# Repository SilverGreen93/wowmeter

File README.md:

# Wow and Flutter meter

Implements the schematic found in Audio Magazine, year 1986, issue 6 to build a simple Wow and Flutter meter.

Contains PCB design.

This is a fork of https://dev.sigpipe.me/DashieElectronics/wowmeter

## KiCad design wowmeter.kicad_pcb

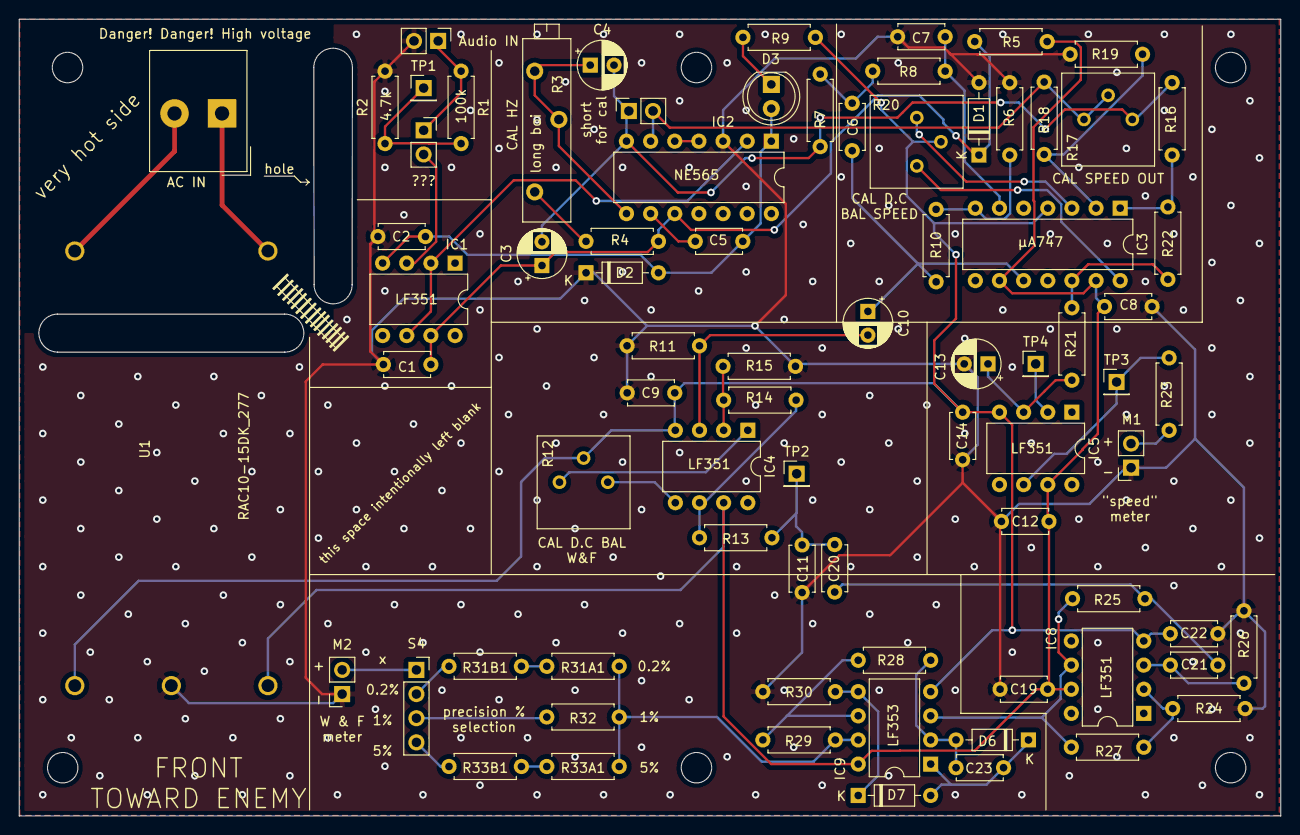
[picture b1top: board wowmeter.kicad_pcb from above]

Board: 2 copper layers, 132.7 x 83.8 mm, 84 parts (0 on the bottom side), 52 nets.

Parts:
C1, C2, C8, C9, C11, C12, C14, C19, C22: 0.022uF cerdisc; C_Disc_D4.7mm_W2.5mm_P5.00mm
C3: 0.1uF; CP_Radial_D5.0mm_P2.50mm
C4: 0.001uF; CP_Radial_D5.0mm_P2.50mm
C5, C6, C7: 0.01uF +-10% sty/mica; C_Disc_D4.7mm_W2.5mm_P5.00mm
C10, C13: 0.22uF; CP_Radial_D5.0mm_P2.50mm
C20, C21: 0.22uF +=10%; C_Disc_D4.7mm_W2.5mm_P5.00mm
C23: 100pF cerdisc; C_Disc_D4.7mm_W2.5mm_P5.00mm
D1, D2: 6V 500mW zener; D_DO-35_SOD27_P7.62mm_Horizontal
D3: LED; LED_D5.0mm
D6, D7: 1N4148; D_DO-35_SOD27_P7.62mm_Horizontal
H1, H2, H3, H4, H5, H6: MountingHole; MountingHole_3.2mm_M3
IC1, IC4, IC5, IC8: LF351; DIP-8_W7.62mm
IC2: NE565; DIP-14_W7.62mm
IC3: µA747; DIP-14_W7.62mm
IC9: LF353; DIP-8_W7.62mm
J1: Audio IN; PinHeader_1x02_P2.54mm_Vertical
J2: CAL_JMP; PinSocket_1x02_P2.54mm_Vertical
J3: AC IN; Altech_AK300_1x02_P5.00mm_45-Degree
M1: 50-0-50µA microammeter; PinSocket_1x02_P2.54mm_Vertical
M2: 0-50µA microammeter; PinSocket_1x02_P2.54mm_Vertical
R1, R23: 100k; R_Axial_DIN0207_L6.3mm_D2.5mm_P7.62mm_Horizontal
R2, R13, R30: 4.7k; R_Axial_DIN0207_L6.3mm_D2.5mm_P7.62mm_Horizontal
R3: 10k, 15T; Potentiometer_Bourns_3006P_Horizontal
R4: 5.6k; R_Axial_DIN0207_L6.3mm_D2.5mm_P7.62mm_Horizontal
R5: 560R 1/2w; R_Axial_DIN0207_L6.3mm_D2.5mm_P7.62mm_Horizontal
R6, R24: 13k; R_Axial_DIN0207_L6.3mm_D2.5mm_P7.62mm_Horizontal
R7, R8: 120k; R_Axial_DIN0207_L6.3mm_D2.5mm_P7.62mm_Horizontal
R9: 430R 1/2w; R_Axial_DIN0207_L6.3mm_D2.5mm_P7.62mm_Horizontal
R10, R27: 9.1k; R_Axial_DIN0207_L6.3mm_D2.5mm_P7.62mm_Horizontal
R11, R21: 4.7M; R_Axial_DIN0207_L6.3mm_D2.5mm_P7.62mm_Horizontal
R12, R20: 10k single-turn; Potentiometer_Bourns_3386P_Vertical
R14: 43k; R_Axial_DIN0207_L6.3mm_D2.5mm_P7.62mm_Horizontal
R15: 1k; R_Axial_DIN0207_L6.3mm_D2.5mm_P7.62mm_Horizontal
R16, R18, R28, R29: 10k; R_Axial_DIN0207_L6.3mm_D2.5mm_P7.62mm_Horizontal
R17: 47k single-turn; Potentiometer_Bourns_3386P_Vertical
R19, R22: 750k; R_Axial_DIN0207_L6.3mm_D2.5mm_P7.62mm_Horizontal
R25, R26: 1.5M; R_Axial_DIN0207_L6.3mm_D2.5mm_P7.62mm_Horizontal
R31A1: 5.1k; R_Axial_DIN0207_L6.3mm_D2.5mm_P7.62mm_Horizontal
R31B1: 200R; R_Axial_DIN0207_L6.3mm_D2.5mm_P7.62mm_Horizontal
R32: 33k; R_Axial_DIN0207_L6.3mm_D2.5mm_P7.62mm_Horizontal
R33A1: 160k; R_Axial_DIN0207_L6.3mm_D2.5mm_P7.62mm_Horizontal
R33B1: 8.2k; R_Axial_DIN0207_L6.3mm_D2.5mm_P7.62mm_Horizontal
S2: ???; PinSocket_1x02_P2.54mm_Vertical
S4: W & F scale; PinSocket_1x04_P2.54mm_Vertical
TP1: TestPoint; PinHeader_1x01_P2.54mm_Vertical
TP2: WOW_OUT; PinHeader_1x01_P2.54mm_Vertical
TP3: SPEED-_OUT; PinHeader_1x01_P2.54mm_Vertical
TP4: SPEED+_OUT; PinHeader_1x01_P2.54mm_Vertical
U1: RAC10-15DK_277

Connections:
+15V: C8.1, C12.1, C19.2, IC3.9, IC3.13, IC4.7, IC5.7, IC8.7, IC9.8, R5.1, U1.5
-15V: C9.1, C14.1, C22.1, IC3.4, IC4.4, IC5.4, IC8.4, IC9.4, R9.1, R12.2, R20.2, U1.3
/0.2%: R31B1.2, S4.2
/1%: R32.2, S4.3
/5%: R33B1.2, S4.4
GND: C1.2, C2.2, C7.2, C8.2, C9.2, C11.2, C12.2, C13.2, C14.2, C19.1, C22.2, D1.2, D2.1, IC2.3, J1.2, M1.1, M2.1, R2.2, R6.2, R11.2, R15.1, R19.1, R24.2, R26.2, R30.2, U1.4
unnamed: C1.1, C3.1, D1.1, IC1.7, IC2.10, R4.1, R5.2
unnamed: C2.1, C5.2, D2.2, D3.2, IC1.4, IC2.1
unnamed: C3.2, C4.2, IC2.7, J2.1, R7.2, R16.2, R17.1
unnamed: C4.1, IC2.8, R3.2, R3.3
unnamed: C5.1, IC2.9
unnamed: C6.1, R7.1, R8.2
unnamed: C7.1, IC3.6, R8.1
unnamed: C6.2, C10.1, IC3.10, R10.2
unnamed: C10.2, IC4.3, R11.1
unnamed: C13.1, IC5.3, R21.1
unnamed: C20.1, C21.2, R25.1
unnamed: C21.1, IC8.3, R26.1
unnamed: C23.1, D6.2, IC9.2, R28.2
unnamed: C23.2, D6.1, D7.2, IC9.1
unnamed: D3.1, R9.2
unnamed: D7.1, IC9.5, R30.1
unnamed: IC1.2, IC1.6, IC2.2
unnamed: IC1.3, S2.2
unnamed: IC2.4, IC2.5
unnamed: IC2.6, J2.2, R17.2, R17.3, R18.2
unnamed: IC3.1, R16.1, R22.2
unnamed: IC3.2, R18.1, R19.2
unnamed: IC3.3, R20.3
unnamed: IC3.7, R6.1, R10.1
unnamed: IC3.12, R21.2, R22.1
unnamed: IC3.14, R20.1
unnamed: IC4.1, R12.3
unnamed: IC4.2, R14.1, R15.2
unnamed: IC4.5, R12.1
unnamed: IC4.6, R13.2, R14.2
unnamed: IC5.2, TP4.1
unnamed: IC8.2, R24.1, R27.1
unnamed: IC8.6, IC9.3, R25.2, R27.2
unnamed: IC9.6, R28.1, R29.2
unnamed: IC9.7, R29.1, R31A1.1, R32.1, R33A1.1
unnamed: J1.1, R1.1, S2.1
unnamed: J3.1, U1.1
unnamed: J3.2, U1.2
unnamed: M1.2, R23.1
unnamed: M2.2, S4.1
unnamed: R1.2, R2.1, TP1.1
unnamed: R3.1, R4.2
unnamed: R31A1.2, R31B1.1
unnamed: R33A1.2, R33B1.1
SPEED_METER: IC5.6, R23.2, TP3.1
WOW_METER: C11.1, C20.2, R13.1, TP2.1

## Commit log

2020-08-02 squeak initial
2020-08-02 oops
2020-08-02 Finished routing the PCB
2020-09-29 Ground plane + stitch
2020-10-15 prout
